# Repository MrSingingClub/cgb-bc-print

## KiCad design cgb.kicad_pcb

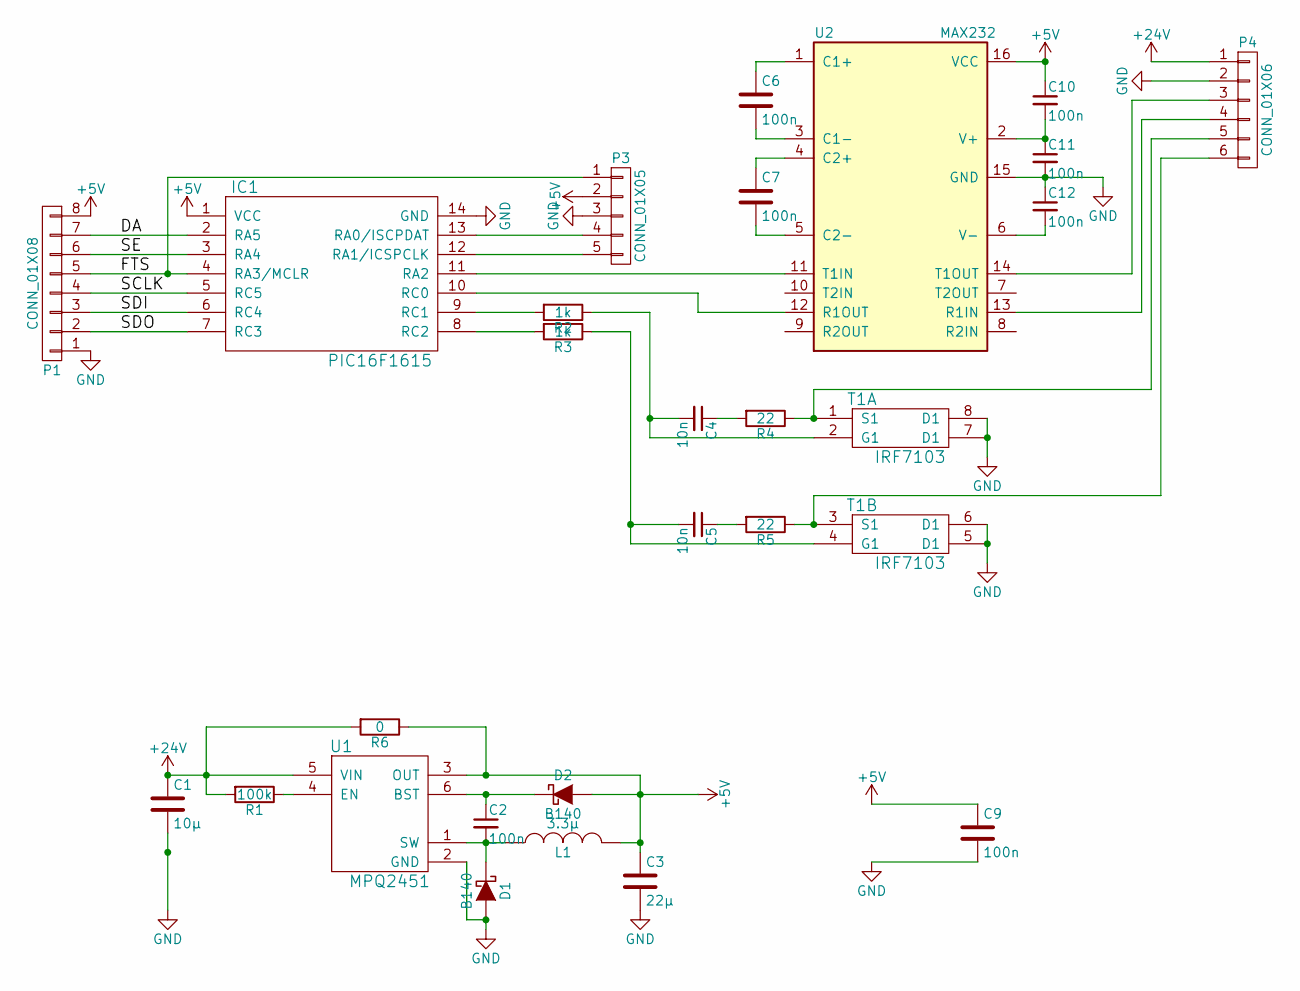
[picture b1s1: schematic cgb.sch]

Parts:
C1: 10µ; C_0805_HandSoldering
C2, C6, C7, C9, C10, C11, C12: 100n; C_0805_HandSoldering
C3: 22µ; C_0805_HandSoldering
C4, C5: 10n; C_0805_HandSoldering
D1, D2: B140; SMA-4
IC1: PIC16F1615; TSSOP-14_4.4x5mm_Pitch0.65mm
L1: 3.3µ; inductorsmd
P1: CONN_01X08; Pin_Header_Straight_1x08_Pitch2.54mm
P3: CONN_01X05; Pin_Header_Straight_1x05_Pitch2.54mm
P4: CONN_01X06; Pin_Header_Straight_1x06_Pitch2.54mm
R1: 100k; R_0805_HandSoldering
R2, R3: 1k; R_0805_HandSoldering
R4, R5: 22; R_0805_HandSoldering
R6: 0; R_0805_HandSoldering
T1: IRF7103; SOIC-8-N
U1: MPQ2451; SOT-23-6_Handsoldering
U2: MAX232; SO-16-N

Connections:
+5V: C3.1, C9.1, C10.1, D2.2 (A), IC1.1 (VCC), L1.2, P1.8, P3.2, R6.1, U1.3 (OUT), U2.16 (VCC)
+24V: C1.1, P4.1, R1.2, R6.2, U1.5 (VIN)
/DA: IC1.2 (RA5), P1.7
/FTS: IC1.4 (RA3/MCLR), P1.5, P3.1
/SCLK: IC1.5 (RC5), P1.4
/SDI: IC1.6 (RC4), P1.3
/SDO: IC1.7 (RC3), P1.2
/SE: IC1.3 (RA4), P1.6
GND: C1.2, C3.2, C9.2, C11.2, C12.1, D1.2 (A), IC1.14 (GND), P1.1, P3.3, P4.2, T1.5 (D1), T1.6 (D1), T1.7 (D1), T1.8 (D1), U1.2 (GND), U2.15 (GND)
unnamed: C2.1, D2.1 (K), U1.6 (BST)
unnamed: C2.2, D1.1 (K), L1.1, U1.1 (SW)
unnamed: C4.1, R4.2
unnamed: C4.2, R2.1, T1.2 (G1)
unnamed: C5.1, R5.2
unnamed: C5.2, R3.1, T1.4 (G1)
unnamed: C6.1, U2.1 (C1+)
unnamed: C6.2, U2.3 (C1-)
unnamed: C7.1, U2.4 (C2+)
unnamed: C7.2, U2.5 (C2-)
unnamed: C10.2, C11.1, U2.2 (V+)
unnamed: C12.2, U2.6 (V-)
unnamed: IC1.8 (RC2), R3.2
unnamed: IC1.9 (RC1), R2.2
unnamed: IC1.10 (RC0), U2.12 (R1OUT)
unnamed: IC1.11 (RA2), U2.11 (T1IN)
unnamed: IC1.12 (RA1/ICSPCLK), P3.5
unnamed: IC1.13 (RA0/ISCPDAT), P3.4
unnamed: P4.3, U2.14 (T1OUT)
unnamed: P4.4, U2.13 (R1IN)
unnamed: P4.5, R4.1, T1.1 (S1)
unnamed: P4.6, R5.1, T1.3 (S1)
unnamed: R1.1, U1.4 (EN)

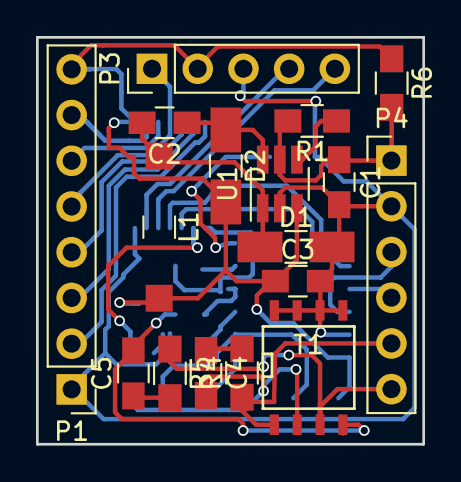
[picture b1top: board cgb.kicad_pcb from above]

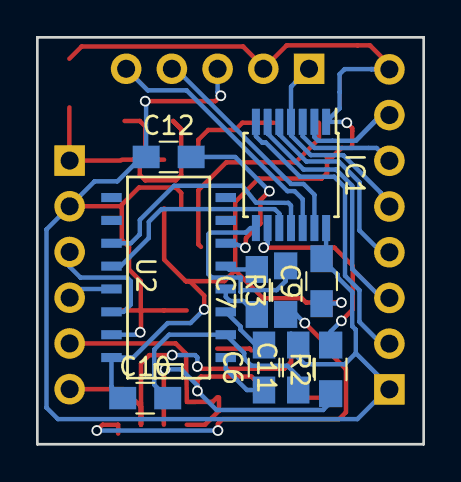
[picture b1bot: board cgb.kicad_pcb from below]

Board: 2 copper layers, 21.5 x 22.6 mm, 27 parts (10 on the bottom side), 32 nets.

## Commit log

2017-05-31 initaler commit
